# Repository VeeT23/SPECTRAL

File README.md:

# SPECTRAL

Short description of the embedded system and what it does.

## Overview

SPECTRAL is a performance line following robot 

## Hardware

### Main Components

| Component          | Part Number       | Description                                                                       |
| ------------------ | ----------------- | --------------------------------------------------------------------------------- |
| MCU                | ESP32-WROOM-32UE  | Main microcontroller                                                              |
| Orientation Sensor | BNO055            | 9-DoF absolute orientation sensor with accelerometer, gyroscope, and magnetometer |
| Motor Controller   | ODrive Micro      | 100 W BLDC motor controller                                                       |
| Motor              | Flash Hobby D4215 | 4215 650 KV BLDC motor, 3S–6S                                                     |
| CAN Transceiver    | ATA6561           | CAN transceiver for motor controller communication                                |

### Pinout

## Pin Definitions

| GPIO | Function | Interface      | Notes                              |
| ---: | -------- | -------------- | ---------------------------------- |
|   16 | A0       | Sensor Address | Sensor address select              |
|   17 | A1       | Sensor Address | Sensor address select              |
|   18 | A2       | Sensor Address | Sensor address select              |
|   32 | S0       | Sensor Output  | Sensor output                      |
|   33 | S1       | Sensor Output  | Sensor output                      |
|   34 | S2       | Sensor Output  | Sensor output                      |
|   35 | S3       | Sensor Output  | Sensor output                      |
|   39 | S4       | Sensor Output  | Sensor output                      |
|   19 | CAN_STBY | CAN            | CAN transceiver standby control    |
|    4 | CAN_RX   | CAN            | CAN receive                        |
|    5 | CAN_TX   | CAN            | CAN transmit                       |
|   22 | SDA      | I2C            | I2C data                           |
|   21 | SCL      | I2C            | I2C clock                          |
|   25 | BUZZER   | GPIO           | Buzzer control                     |
|   26 | NEOPIXEL | GPIO           | Exposed on board; currently unused |
|   27 | FAN_PWM  | PWM            | Exposed on board; currently unused |

## Software

### Toolchain

- **Platform:** Espressif32
- **MCU:** ESP32-WROOM-32UE
- **Framework:** Arduino
- **Build System:** PlatformIO
- **IDE:** Visual Studio Code + PlatformIO

## Repository Structure

```text
SPECTRAL/
├── firmware/
│   ├── common/
│   ├── control_station_firmware/
│   └── spectral_firmware/
├── hardware/
│   ├── main_board/
│   ├── power_module/
│   └── sensor_module/
├── .gitignore
└── README.md
```

## Configuration

| Parameter                |               Value | Description                                        |
| ------------------------ | ------------------: | -------------------------------------------------- |
| Control Frequency        |             1000 Hz | Main control loop frequency                        |
| Display Update Period    |               40 ms | Period between display updates                     |
| Wheel Spacing            |              104 mm | Distance between drive wheels                      |
| Wheel Diameter           |               60 mm | Drive wheel diameter                               |
| Wheel Circumference      |            0.1885 m | Calculated wheel circumference                     |
| Line Following Kp        |                 1.0 | Proportional gain                                  |
| Line Following Ki        |                0.01 | Integral gain                                      |
| Line Following Kd        |                0.01 | Derivative gain                                    |
| Number of Sensor Modules |                   5 | Number of IR sensor modules                        |
| Sensors per Module       |                   8 | Number of sensors on each module                   |
| Total IR Sensors         |                  40 | Total number of IR sensors                         |
| IR Threshold             |                2000 | Sensor threshold used for line detection           |
| Controller MAC           | `D8:3B:DA:46:57:80` | MAC address of the remote controller               |
| Radio RX Timeout         |             1000 ms | Maximum time without receiving controller data     |
| Telemetry Frequency      |              120 Hz | Telemetry transmission frequency                   |
| Radio Debug              |            Disabled | Enables/disables radio debug output                |
| CAN Bitrate              |          500 kbit/s | CAN bus communication speed                        |
| CAN TX Timeout           |               40 ms | Maximum time to wait for CAN transmission          |
| Serial Baud Rate         |              115200 | Serial communication baud rate                     |
| ODrive Heartbeat Timeout |              200 ms | Maximum time without receiving an ODrive heartbeat |
| Motors Enabled           |                 Yes | Enables motor operation                            |

### ODrive Commands

The following CAN command IDs are used to communicate with the ODrive motor controller:

| Command              | CAN ID | Description                                |
| -------------------- | -----: | ------------------------------------------ |
| Heartbeat            | `0x01` | ODrive heartbeat                           |
| Emergency Stop       | `0x02` | Trigger emergency stop                     |
| Set Axis State       | `0x07` | Change ODrive axis state                   |
| Get Encoder Estimate | `0x09` | Request encoder position/velocity estimate |
| Set Input Velocity   | `0x0D` | Set motor velocity command                 |
| Clear Errors         | `0x18` | Clear ODrive errors                        |

### ODrive Axis States

| State       | Value | Description                           |
| ----------- | ----: | ------------------------------------- |
| Idle        |   `1` | Motor disabled / idle                 |
| Closed Loop |   `8` | Motor enabled for closed-loop control |

## Power

Spectral uses a 450 mAh 3s 75C lipo
Running power is unknown however the circuit supports up to 10A continous.
Idle power is measured to be ~140ma

WARNING: AS IT STANDS CURRENTLY, SPECTRAL LACKS OVER DISCHARGE PROTECTION, MONITOR BATTERY VOLTAGE BETWEEN RUNS TO AVOID DAMAGE TO THE BATTERY

## Communication

* UART - Serial debugging/flashing
* I2C - Display screen
* CAN - Motor controllers
* ESP-NOW - Base station communication

## Known Issues

* Dynamic velocity control has no smoothing between setpoints
* Power module lacks battery monitoring for undervoltage

## Future Work

This project is closed, however I will add documentation/clean up issues on request. 

## License

This project is licensed under the GNU GENERAL PUBLIC LICENSE.

## Author

**Veronica Tobias**

[GitHub](https://github.com/VeeT23)

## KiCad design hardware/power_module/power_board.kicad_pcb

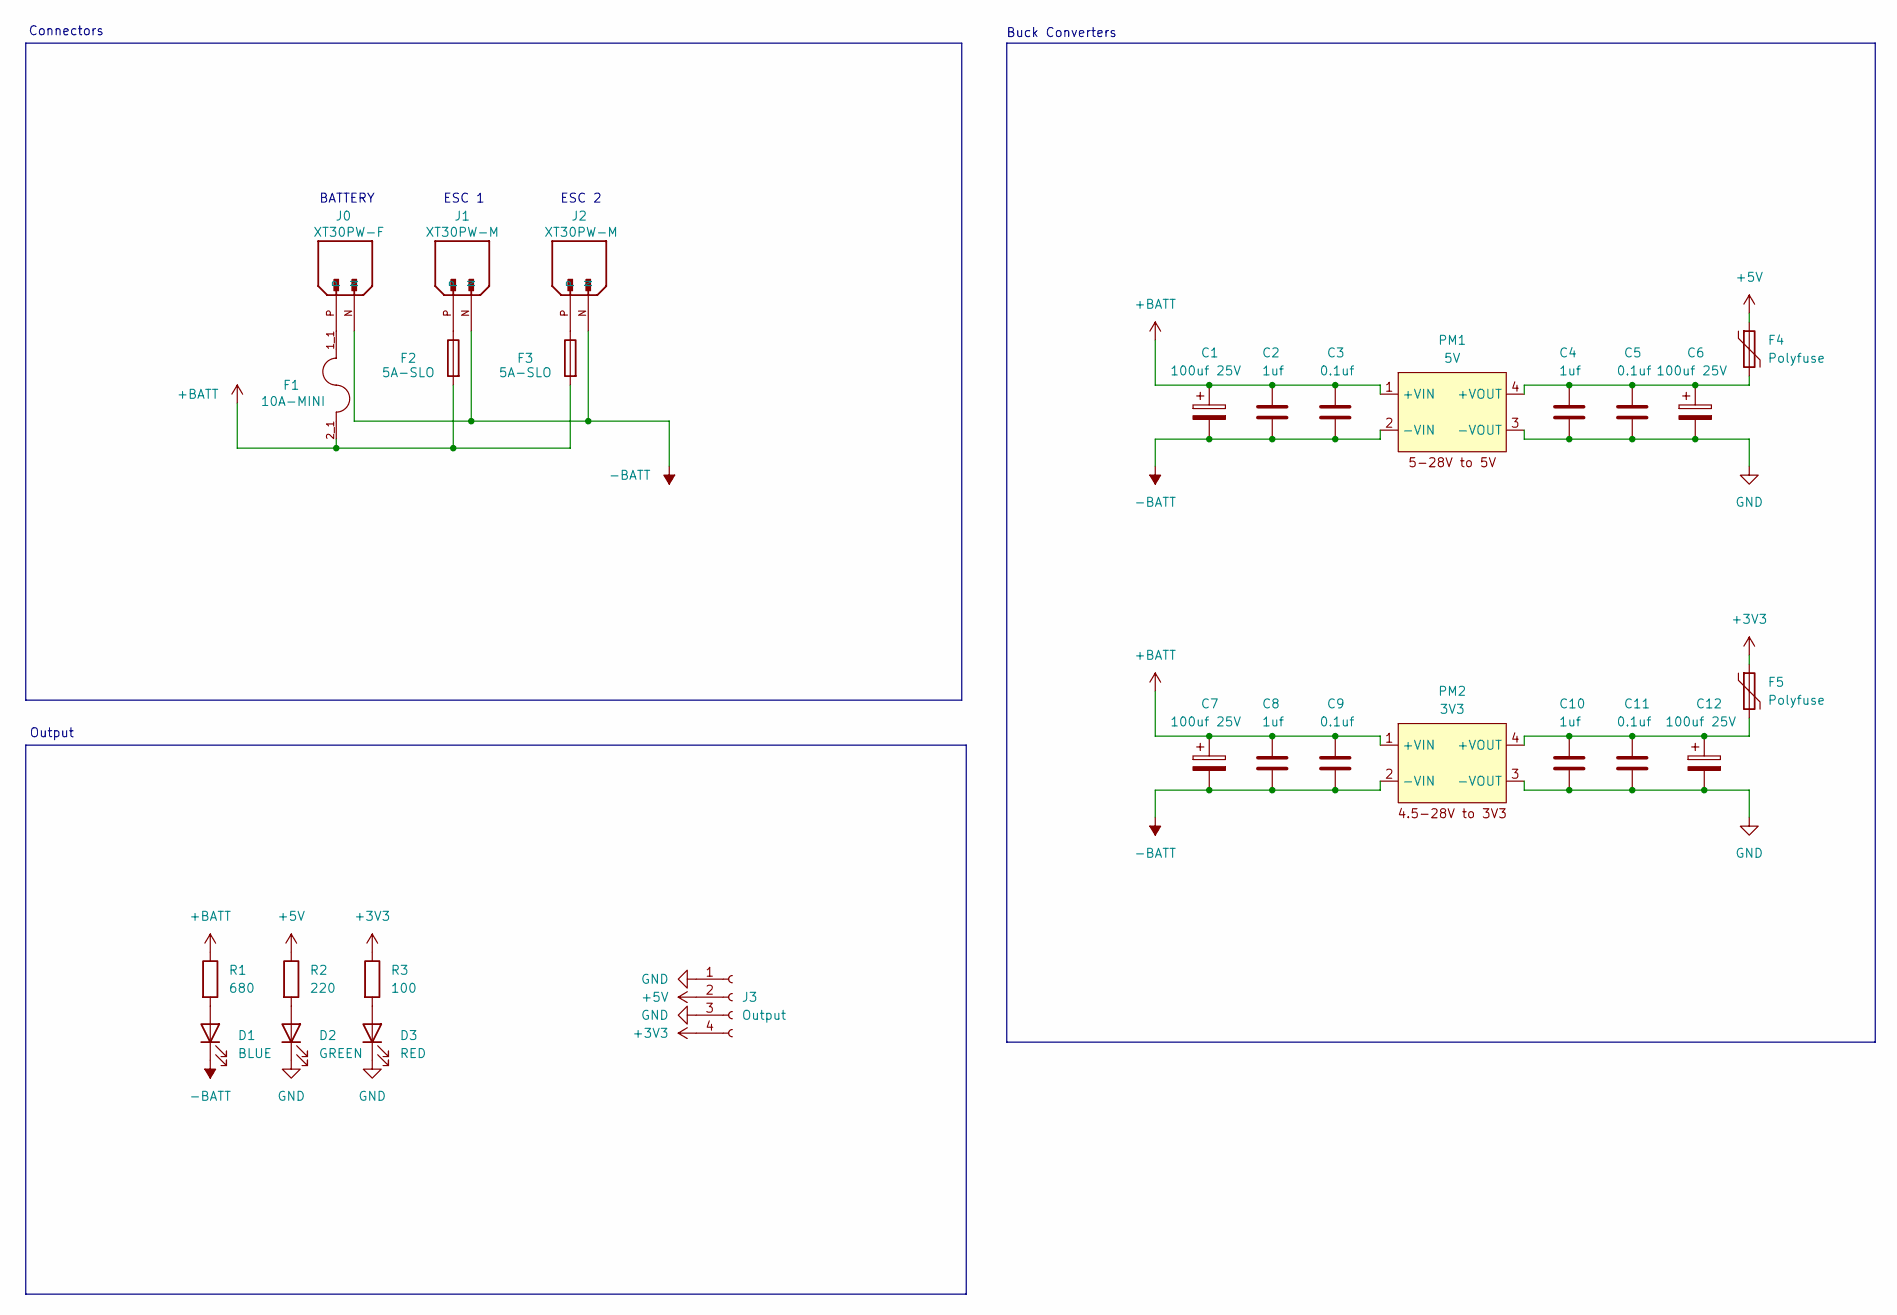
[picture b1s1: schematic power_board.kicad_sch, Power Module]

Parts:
C1, C6, C7, C12: 100uf 25V; CP_Radial_D5.0mm_P2.00mm
C2, C4, C8, C10: 1uf; C_0603_1608Metric_Pad1.08x0.95mm_HandSolder
C3, C5, C9, C11: 0.1uf; C_0603_1608Metric_Pad1.08x0.95mm_HandSolder
D1: BLUE; LED_0603_1608Metric_Pad1.05x0.95mm_HandSolder
D2: GREEN; LED_0603_1608Metric_Pad1.05x0.95mm_HandSolder
D3: RED; LED_0603_1608Metric_Pad1.05x0.95mm_HandSolder
F1: 10A-MINI; FUSE_3549-2; PARTREV D; DigiKey_Part_Number 36-3549-2-ND
F2, F3: 5A-SLO; Fuse_1206_3216Metric_Pad1.42x1.75mm_HandSolder
F4, F5: Polyfuse; Fuse_2920_7451Metric_Pad2.10x5.45mm_HandSolder
J0: XT30PW-F; AMASS_XT30PW-M; PARTREV 1.2
J1, J2: XT30PW-M; AMASS_XT30PW-M; PARTREV 1.2
J3: Output; JST_GH_BM04B-GHS-TBT_1x04-1MP_P1.25mm_Vertical
PM1: 5V; DC_Buck_Module
PM2: 3V3; DC_Buck_Module
R1: 680; R_0603_1608Metric_Pad0.98x0.95mm_HandSolder
R2: 220; R_0603_1608Metric_Pad0.98x0.95mm_HandSolder
R3: 100; R_0603_1608Metric_Pad0.98x0.95mm_HandSolder

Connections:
+3V3: F5.1, J3.4, R3.1
+5V: F4.1, J3.2, R2.1
+BATT: C1.1, C2.1, C3.1, C7.1, C8.1, C9.1, F1.2_1, F1.2_2, F2.2, F3.2, PM1.1 (+VIN), PM2.1 (+VIN), R1.1
-BATT: C1.2, C2.2, C3.2, C7.2, C8.2, C9.2, D1.1 (K), J0.N, J0.S1, J0.S2, J1.N, J1.S1, J1.S2, J2.N, J2.S1, J2.S2, PM1.2 (-VIN), PM2.2 (-VIN)
GND: C4.2, C5.2, C6.2, C10.2, C11.2, C12.2, D2.1 (K), D3.1 (K), J3.1, J3.3, J3.MP, PM1.3 (-VOUT), PM2.3 (-VOUT)
unnamed: D1.2 (A), R1.2
unnamed: D2.2 (A), R2.2
unnamed: D3.2 (A), R3.2
unnamed: F1.1_1, F1.1_2, J0.P
unnamed: F2.1, J1.P
unnamed: F3.1, J2.P
unnamed: C4.1, C5.1, C6.1, F4.2, PM1.4 (+VOUT)
unnamed: C10.1, C11.1, C12.1, F5.2, PM2.4 (+VOUT)

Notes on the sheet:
BATTERY
Connectors
ESC 1
ESC 2
Buck Converters
Output

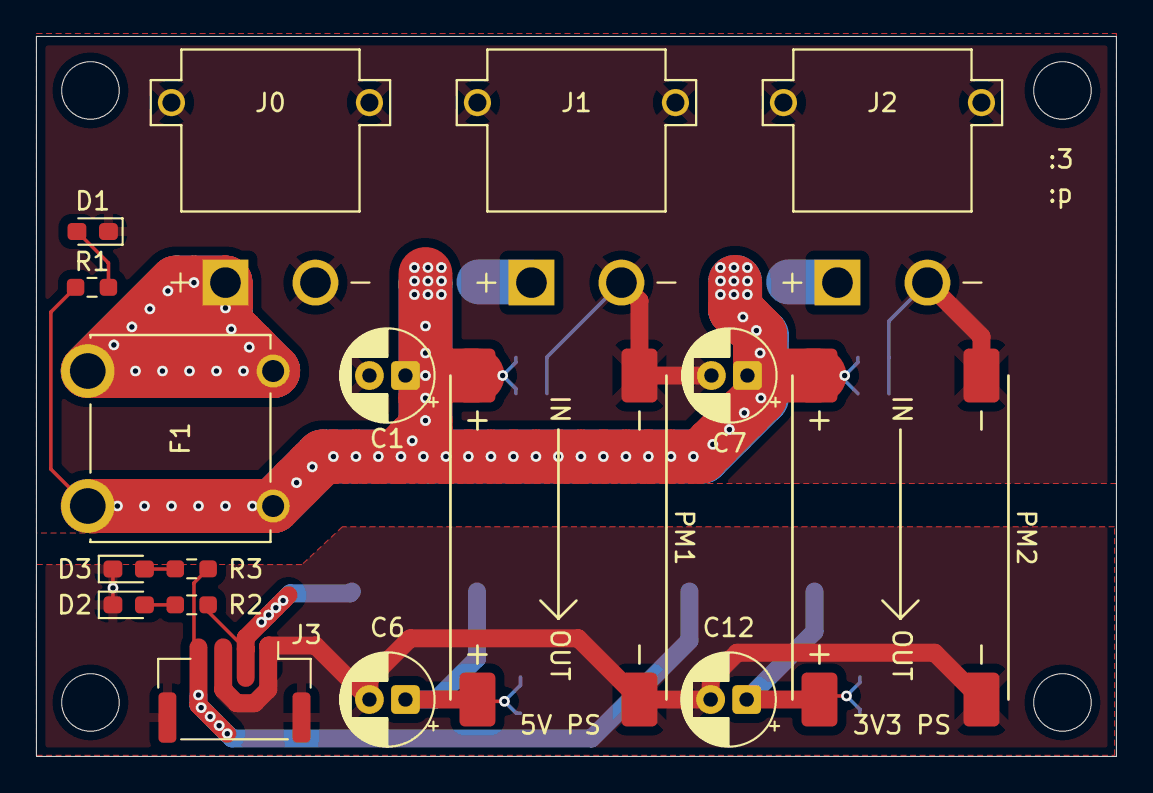
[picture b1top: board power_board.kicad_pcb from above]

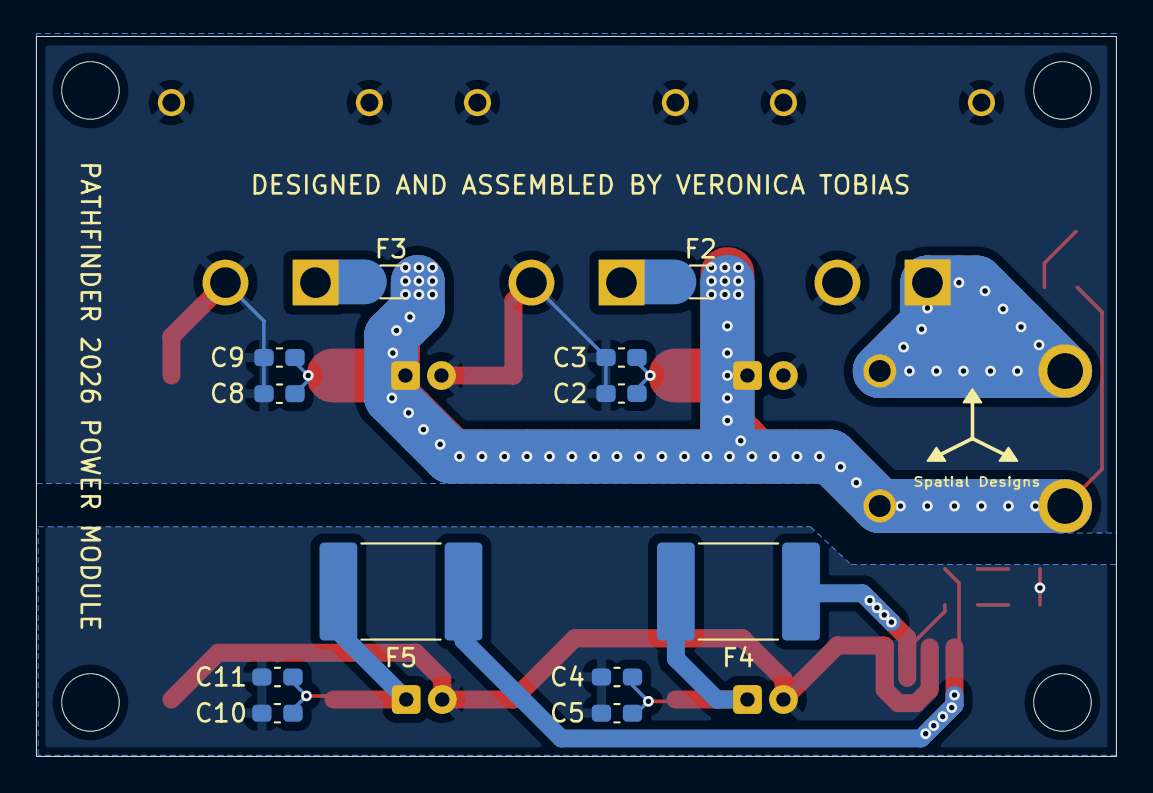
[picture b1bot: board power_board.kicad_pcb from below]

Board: 2 copper layers, 60.0 x 40.0 mm, 29 parts (12 on the bottom side), 13 nets.

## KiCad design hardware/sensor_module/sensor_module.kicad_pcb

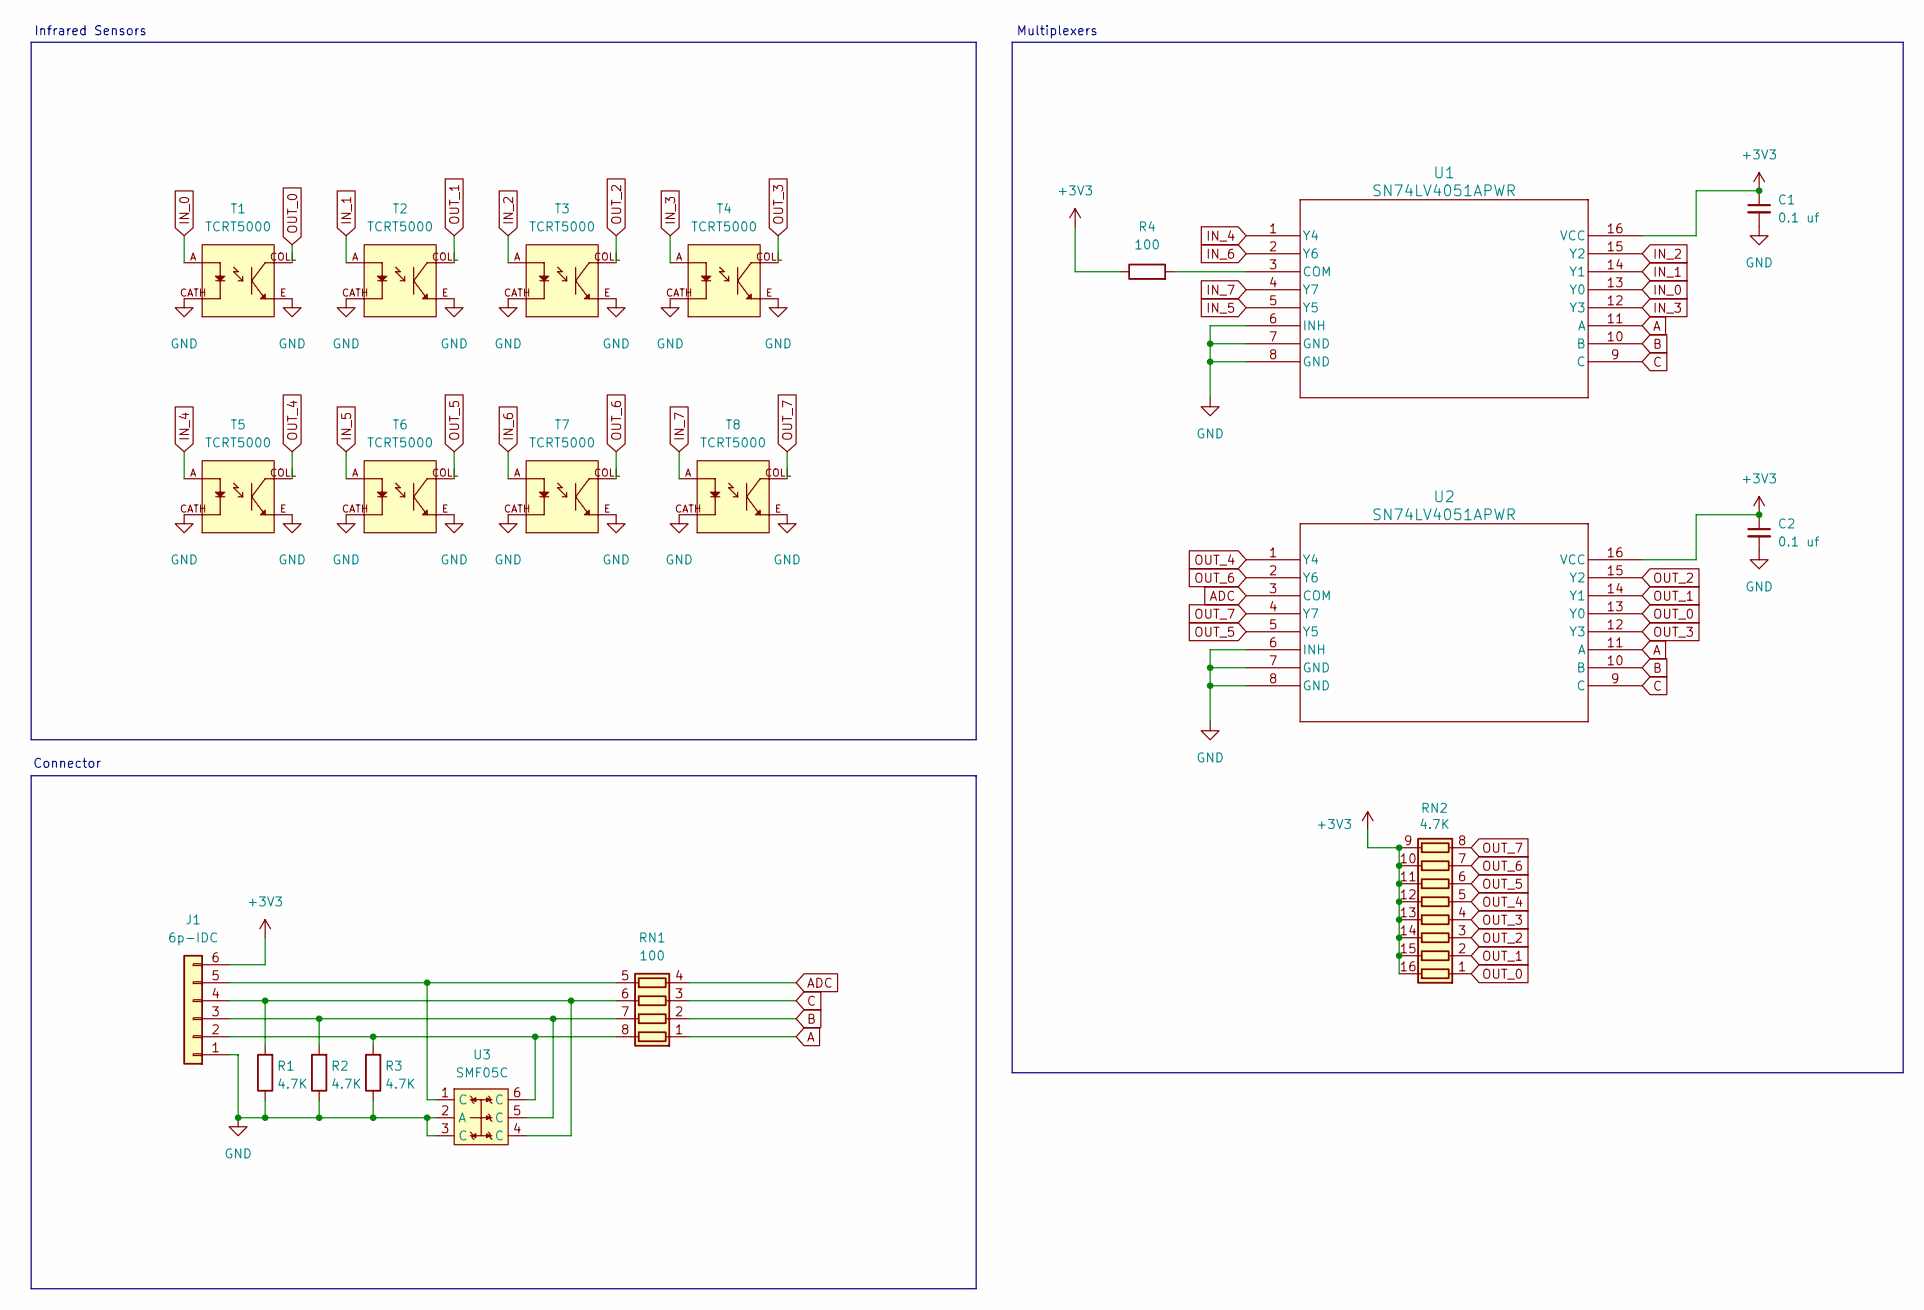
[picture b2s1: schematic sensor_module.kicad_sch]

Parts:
C1, C2: 0.1 uf; C_0603_1608Metric_Pad1.08x0.95mm_HandSolder
J1: 6p-IDC; CONN_SM06B-GHS-TB_JST
R1, R2, R3: 4.7K; R_0603_1608Metric_Pad0.98x0.95mm_HandSolder
R4: 100; R_0603_1608Metric_Pad0.98x0.95mm_HandSolder
RN1: 100; EXB28V_PAN-L
RN2: 4.7K; RES_EXB2HV
T1, T2, T3, T4, T5, T6, T7, T8: TCRT5000; TCRT5000-MINI; PARTREV 1.7
U1, U2: SN74LV4051APWR; PW16
U3: SMF05C; SOT-363_SC-70-6_Handsoldering

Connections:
+3V3: C1.1, C2.1, J1.6, R4.1, RN2.9 (R8.2), RN2.10 (R7.2), RN2.11 (R6.2), RN2.12 (R5.2), RN2.13 (R4.2), RN2.14 (R3.2), RN2.15 (R2.2), RN2.16 (R1.2), U1.16 (VCC), U2.16 (VCC)
A: RN1.1 (R1.1), U1.11 (A), U2.11 (A)
ADC: RN1.4 (R4.1), U2.3 (COM)
B: RN1.2 (R2.1), U1.10 (B), U2.10 (B)
C: RN1.3 (R3.1), U1.9 (C), U2.9 (C)
GND: C1.2, C2.2, J1.1, R1.1, R2.1, R3.1, T1.CATH, T1.E, T2.CATH, T2.E, T3.CATH, T3.E, T4.CATH, T4.E, T5.CATH, T5.E, T6.CATH, T6.E, T7.CATH, T7.E, T8.CATH, T8.E, U1.6 (INH), U1.7 (GND), U1.8 (GND), U2.6 (INH), U2.7 (GND), U2.8 (GND), U3.2 (A), U3.3 (C)
IN_0: T1.A, U1.13 (Y0)
IN_1: T2.A, U1.14 (Y1)
IN_2: T3.A, U1.15 (Y2)
IN_3: T4.A, U1.12 (Y3)
IN_4: T5.A, U1.1 (Y4)
IN_5: T6.A, U1.5 (Y5)
IN_6: T7.A, U1.2 (Y6)
IN_7: T8.A, U1.4 (Y7)
unnamed: J1.2, R3.2, RN1.8 (R1.2), U3.6 (C)
unnamed: J1.3, R2.2, RN1.7 (R2.2), U3.5 (C)
unnamed: J1.4, R1.2, RN1.6 (R3.2), U3.4 (C)
unnamed: J1.5, RN1.5 (R4.2), U3.1 (C)
unnamed: R4.2, U1.3 (COM)
OUT_0: RN2.1 (R1.1), T1.COLL, U2.13 (Y0)
OUT_1: RN2.2 (R2.1), T2.COLL, U2.14 (Y1)
OUT_2: RN2.3 (R3.1), T3.COLL, U2.15 (Y2)
OUT_3: RN2.4 (R4.1), T4.COLL, U2.12 (Y3)
OUT_4: RN2.5 (R5.1), T5.COLL, U2.1 (Y4)
OUT_5: RN2.6 (R6.1), T6.COLL, U2.5 (Y5)
OUT_6: RN2.7 (R7.1), T7.COLL, U2.2 (Y6)
OUT_7: RN2.8 (R8.1), T8.COLL, U2.4 (Y7)

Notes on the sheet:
Infrared Sensors
Connector
Multiplexers

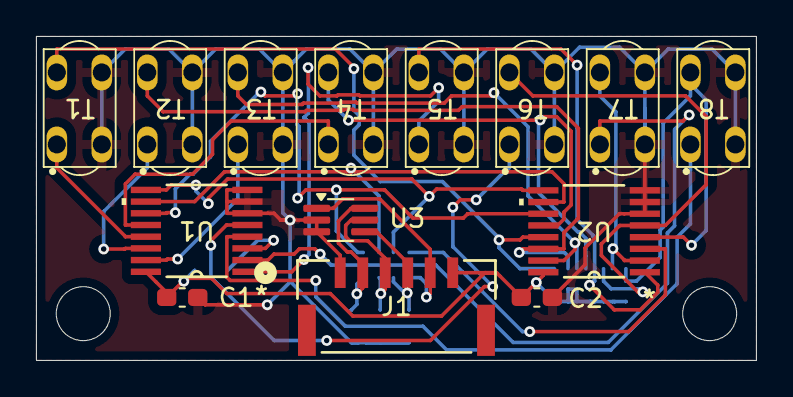
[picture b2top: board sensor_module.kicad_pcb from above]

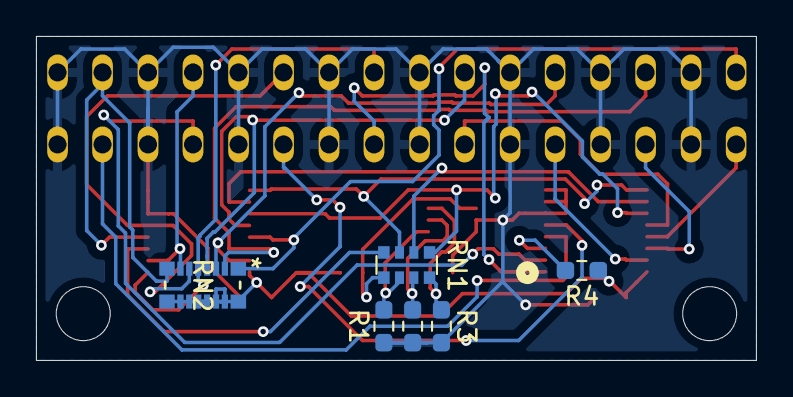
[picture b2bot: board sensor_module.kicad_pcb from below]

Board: 2 copper layers, 40.0 x 18.0 mm, 20 parts (6 on the bottom side), 27 nets.

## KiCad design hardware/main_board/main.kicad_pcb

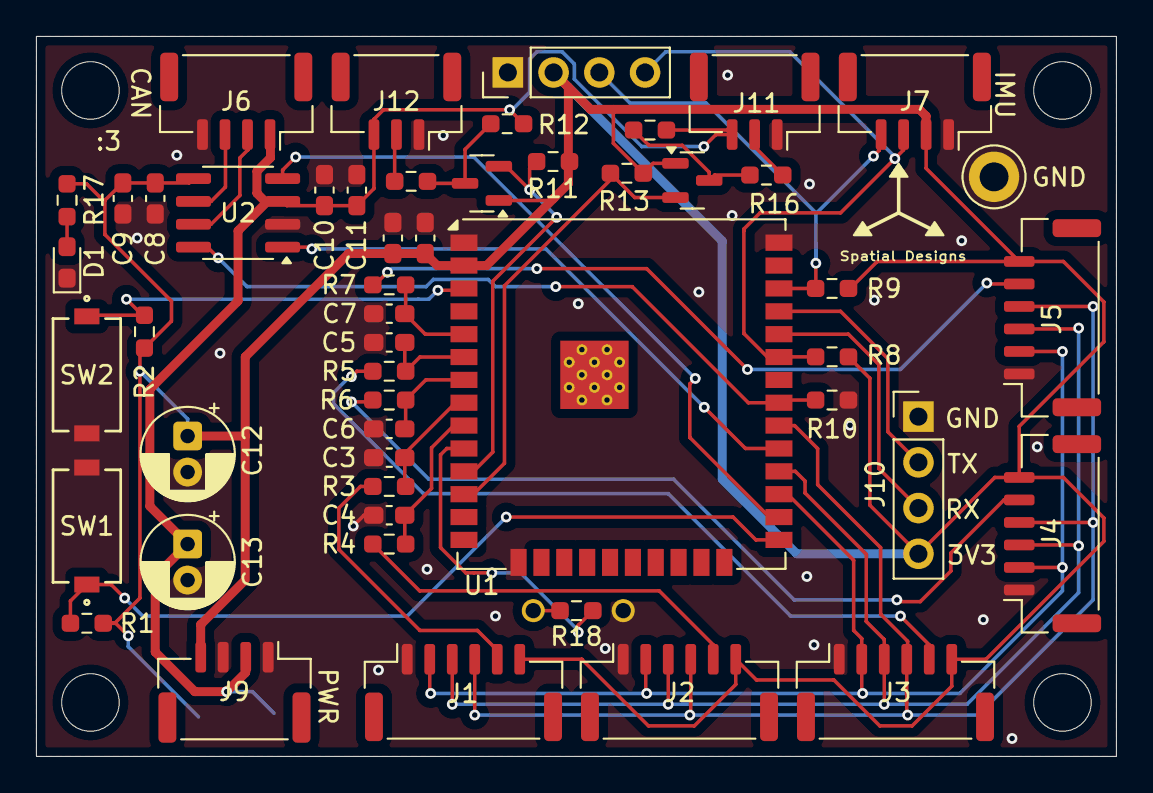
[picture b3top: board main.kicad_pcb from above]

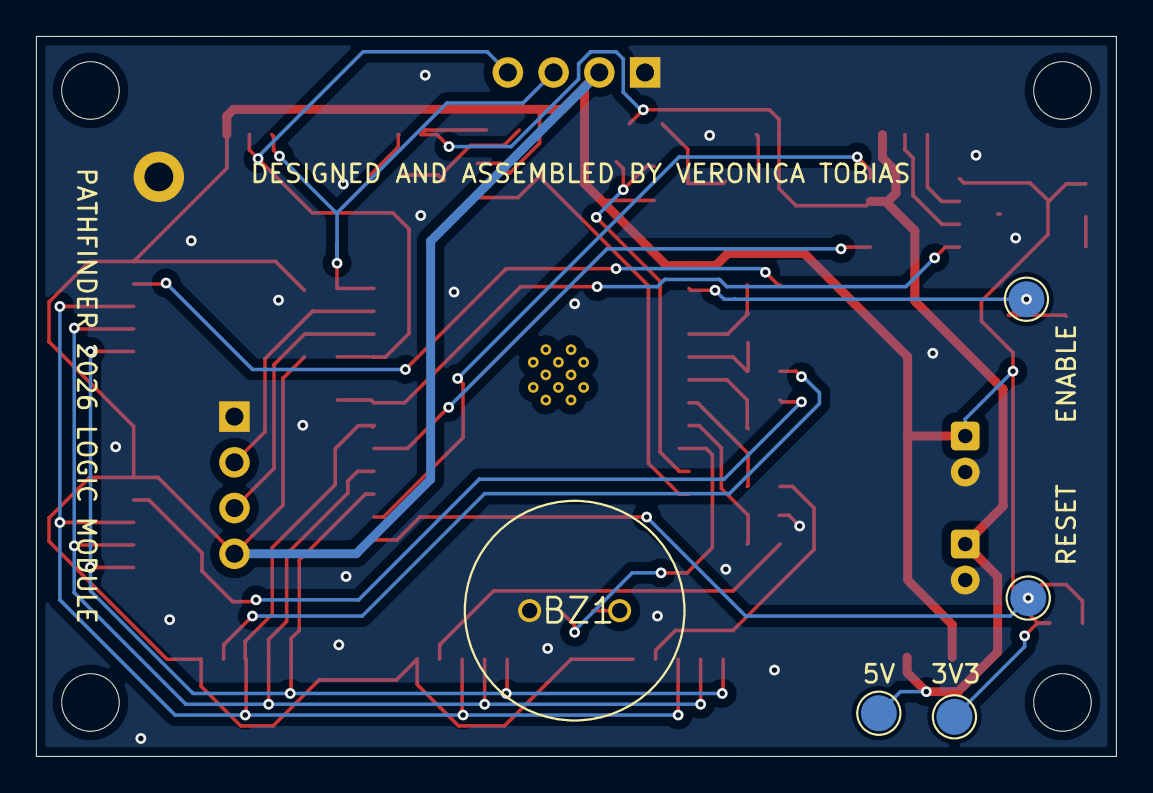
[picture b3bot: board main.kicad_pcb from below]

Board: 2 copper layers, 60.0 x 40.0 mm, 56 parts (5 on the bottom side), 36 nets.

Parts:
BZ1: Buzzer; XDCR_PS1240P02CT3
C1, C8, C10: 0.1uf; C_0603_1608Metric_Pad1.08x0.95mm_HandSolder
C2, C9, C11: 10uf; C_0603_1608Metric_Pad1.08x0.95mm_HandSolder
C3, C4, C5, C6, C7: 1nf; C_0603_1608Metric_Pad1.08x0.95mm_HandSolder
C12, C13: 100uf; CP_Radial_D5.0mm_P2.00mm
D1: RED; LED_0603_1608Metric_Pad1.05x0.95mm_HandSolder
J1: Sensor 1; JST_GH_SM06B-GHS-TB_1x06-1MP_P1.25mm_Horizontal
J2: Sensor 2; JST_GH_SM06B-GHS-TB_1x06-1MP_P1.25mm_Horizontal
J3: Sensor 3; JST_GH_SM06B-GHS-TB_1x06-1MP_P1.25mm_Horizontal
J4: Sensor 4; JST_GH_SM06B-GHS-TB_1x06-1MP_P1.25mm_Horizontal
J5: Sensor 5; JST_GH_SM06B-GHS-TB_1x06-1MP_P1.25mm_Horizontal
J6: CAN; JST_GH_SM04B-GHS-TB_1x04-1MP_P1.25mm_Horizontal
J7: IMU; JST_GH_SM04B-GHS-TB_1x04-1MP_P1.25mm_Horizontal
J8: OLED; PinHeader_1x04_P2.54mm_Vertical
J9: Power; JST_GH_BM04B-GHS-TBT_1x04-1MP_P1.25mm_Vertical
J10: UART; PinHeader_1x04_P2.54mm_Vertical
J11: PWM; JST_GH_SM03B-GHS-TB_1x03-1MP_P1.25mm_Horizontal
J12: NEOPIXEL; JST_GH_SM03B-GHS-TB_1x03-1MP_P1.25mm_Horizontal
Q1, Q4: BSS138; SOT-23
R1, R2, R8, R9, R10, R11, R12, R13, R14: 4.7K; R_0603_1608Metric_Pad0.98x0.95mm_HandSolder
R3, R4, R5, R6, R7, R15, R16, R17, R18: 100; R_0603_1608Metric_Pad0.98x0.95mm_HandSolder
SW1: BOOT; SW_PTS636_CNK
SW2: RESET; SW_PTS636_CNK
TP1: BOOT; TestPoint_Pad_D2.0mm
TP2: EN; TestPoint_Pad_D2.0mm
TP3: 3V3; TestPoint_Pad_D2.0mm
TP4: 5V; TestPoint_Pad_D2.0mm
TP5: GND; TestPoint_Keystone_5005-5009_Compact
U1: ESP32-WROOM-32UE_M113EH6400UH3Q0_; ESP32-WROOM-32UE
U2: ATA6561-GAQW-N; SOIC-8_3.9x4.9mm_P1.27mm

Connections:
+3V3: C1.1, C2.1, C8.1, C9.1, C12.1, J1.6, J2.6, J3.6, J4.6, J5.6, J7.2, J8.2, J9.4, J10.4, Q1.1 (G), Q4.1 (G), R1.1, R2.1, R8.2, R9.2, R11.2, R13.2, R17.1, TP3.1, U1.2 (3V3), U2.5 (VRXD)
+5V: C10.1, C11.1, C13.1, J6.1, J9.2, J11.3, J12.3, R12.2, R14.2, TP4.1, U2.3 (VCC)
A0: J1.2, J2.2, J3.2, J4.2, J5.2, U1.27 (IO16)
A1: J1.3, J2.3, J3.3, J4.3, J5.3, U1.28 (IO17)
A2: J1.4, J2.4, J3.4, J4.4, J5.4, U1.30 (IO18)
BOOT: R1.2, SW1.1, TP1.1, U1.25 (IO0)
BUZZER: R18.1, U1.10 (IO25)
CAN_RX: U1.26 (IO4), U2.4 (RXD)
CAN_STBY: R10.1, U1.31 (IO19), U2.8 (S)
CAN_TX: U1.29 (IO5), U2.1 (TXD)
EN: R2.2, SW2.1, TP2.1, U1.3 (EN)
GND: BZ1.2 (-), C1.2, C2.2, C3.2, C4.2, C5.2, C6.2, C7.2, C8.2, C9.2, C10.2, C11.2, C12.2, C13.2, D1.1 (K), J1.1, J2.1, J3.1, J4.1, J5.1, J6.4, J7.1, J8.1, J9.1, J9.3, J10.1, J11.1, J12.1, R10.2, SW1.2, SW2.2, TP5.1, U1.1 (GND), U1.15 (GND), U1.38 (GND), U2.2 (GND)
NEO: Q4.2 (S), R11.1, U1.11 (IO26)
unnamed: BZ1.1 (+), R18.2
unnamed: D1.2 (A), R17.2
unnamed: J6.2, U2.7 (CANH)
unnamed: J6.3, U2.6 (CANL)
unnamed: J11.2, R16.2
unnamed: J12.2, R15.2
unnamed: Q1.3 (D), R14.1, R16.1
unnamed: Q4.3 (D), R12.1, R15.1
unnamed: C3.1, R3.2, U1.8 (IO32)
unnamed: C4.1, R4.2, U1.9 (IO33)
unnamed: C5.1, R5.1, U1.6 (IO34)
unnamed: C6.1, R6.1, U1.7 (IO35)
unnamed: C7.1, R7.1, U1.5 (SENSOR_VN)
PWM: Q1.2 (S), R13.1, U1.12 (IO27)
RX: J10.3, U1.34 (RXD0)
S0: J1.5, R3.1
S1: J2.5, R4.1
S2: J3.5, R5.2
S3: J4.5, R6.2
S4: J5.5, R7.2
SCL: J7.4, J8.3, R9.1, U1.36 (IO22)
SDA: J7.3, J8.4, R8.1, U1.33 (IO21)
TX: J10.2, U1.35 (TXD0)

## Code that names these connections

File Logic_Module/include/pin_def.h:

#pragma once
namespace PINS {

    //Sensor address pins
    constexpr int A0 = 16;
    constexpr int A1 = 17;
    constexpr int A2 = 18;

    //Sensor output pins
    constexpr int S0 = 32;
    constexpr int S1 = 33;
    constexpr int S2 = 34;
    constexpr int S3 = 35;
    constexpr int S4 = 39;

    //CAN BUS
    constexpr int CAN_STBY = 19;
    constexpr int CAN_RX = 4;
    constexpr int CAN_TX = 5;

    //I2C BUS
    constexpr int SDA = 22;
    constexpr int SCL = 21;

    //Misc
    constexpr int BUZZER = 25;
    constexpr int NEOPIXEL = 26;
    constexpr int FAN_PWM = 27;

}

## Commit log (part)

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2025-12-31 logic mod
2025-12-31 OTA support
2025-12-31 created control and ota headers
2026-01-21 Initial project structure and core modules
    Add core source, include, and configuration files for Control_hub and Logic_Module, including joystick, screen, radio, and packet abstractions. Remove obsolete OTA and receiver code. Update pin defin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
2026-01-28 fixed can
2026-01-31 Refactor
2026-02-01 debug radio
2026-02-01 radio
2026-02-03 update radio
2026-02-04 Mac address maybe?
2026-02-04 control
2026-02-16 Update hardware configs and improve motor/sensor control
    Apply hardware and platform updates (board, upload ports, MACs, pin mappings) and significantly improve motor telemetry, encoder handling, IR processing, and control logic. Key changes:
    - Control_hub: changed ROBOT_MAC, remapped joystick pins to analog (A0..A3), switched platformio board to seeed_xiao_esp32s3 and added upload_port, added serial log when sending commands.
    - Logic_Module config: reduced draw period, added wheel diameter/circumference, MAX_VELOCITY and MAX_REV, updated CONTROLLER_MAC and increased CAN_TX_TIMEOUT.
    - Motor class: track encoder reception, apply inversion/position offset, add zeroPosition() and waitForEncoder
2026-02-19 fixed radio
2026-02-19 data plot
2026-02-21 Refactor telemetry, add visualizer & odometry
    Introduce end-to-end telemetry changes and tooling:
    - Common: expand ControlPacket/TelemetryPacket in Common/include/packet.h (control_mode, per-wheel throttles, ticks_since_idle, packed IR bitfield, line/pid/distance/pose fields).
    - Control hub: improve Joystick (deadzone, just_released, drawing tweaks), change Controller main to support control modes (IDLE/MANUAL/AUTO), send control_mode + per-wheel throttle, emit framed tele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
    - Data_Visualizer: add a new Python visualizer (gui.py, myserial.py, packet.py, main.py) and assets to read framed
2026-02-22 Refactor GUI and extract image/path modules
    Split and refactor the app: add a new gui.py with menu and central widget builders, extract image pipeline into Arc/path_processor.py, and rename pathfinder to path_finder with new helpers. main.py n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
2026-02-23 remove cache
2026-02-25 test
2026-02-25 auto rotation
2026-02-28 rename
2026-03-04 data init
2026-03-06 menu bar + map widgets
    also updated gitignore
2026-03-06 fixed image_processor.py
2026-03-07 color_line and stages control
2026-03-07 added draw path
2026-03-07 remove cache from repo
2026-03-07 Migrated pathfinder to polyline
2026-03-09 reorganized + added packets pipeline and position plotting
2026-03-09 added ir sensor widget
2026-04-15 Add telemetry DB, UI widgets and controller updates
    Large refactor and feature additions across controller firmware and data-analysis UI:
    - Common: add max_velocity to ControlPacket and drawCenteredText helper in Screen.
    - Control station firmware: introduce BASE_VELOCITY and TELEMETRY_HEADER in config; enhance joystick drawing to respect box size and constrain dot to circle; add in-config menu to tune max_velocity, 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
    - ESP32Serial (spectral_data_analysis): move to background threads with a small packe
2026-04-15 highlight sync
2026-04-15 refactor sensor array
    better code encapsulation
    better line detection
    cool beans
2026-05-01 competition rush, idek
